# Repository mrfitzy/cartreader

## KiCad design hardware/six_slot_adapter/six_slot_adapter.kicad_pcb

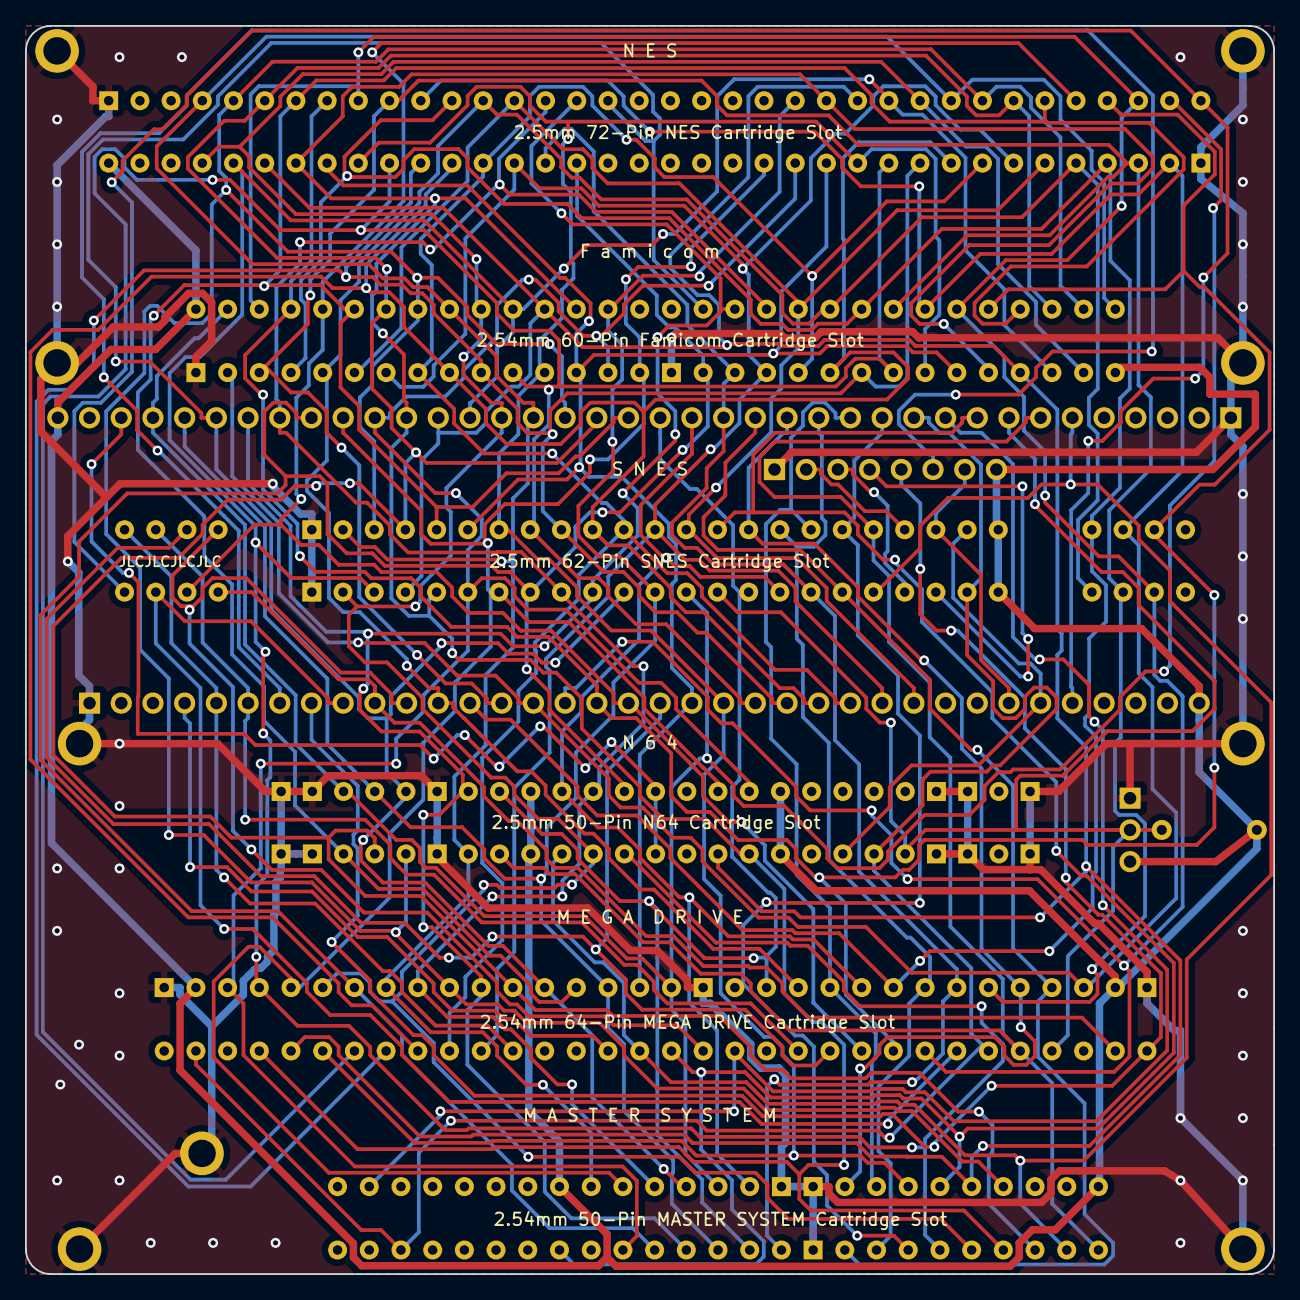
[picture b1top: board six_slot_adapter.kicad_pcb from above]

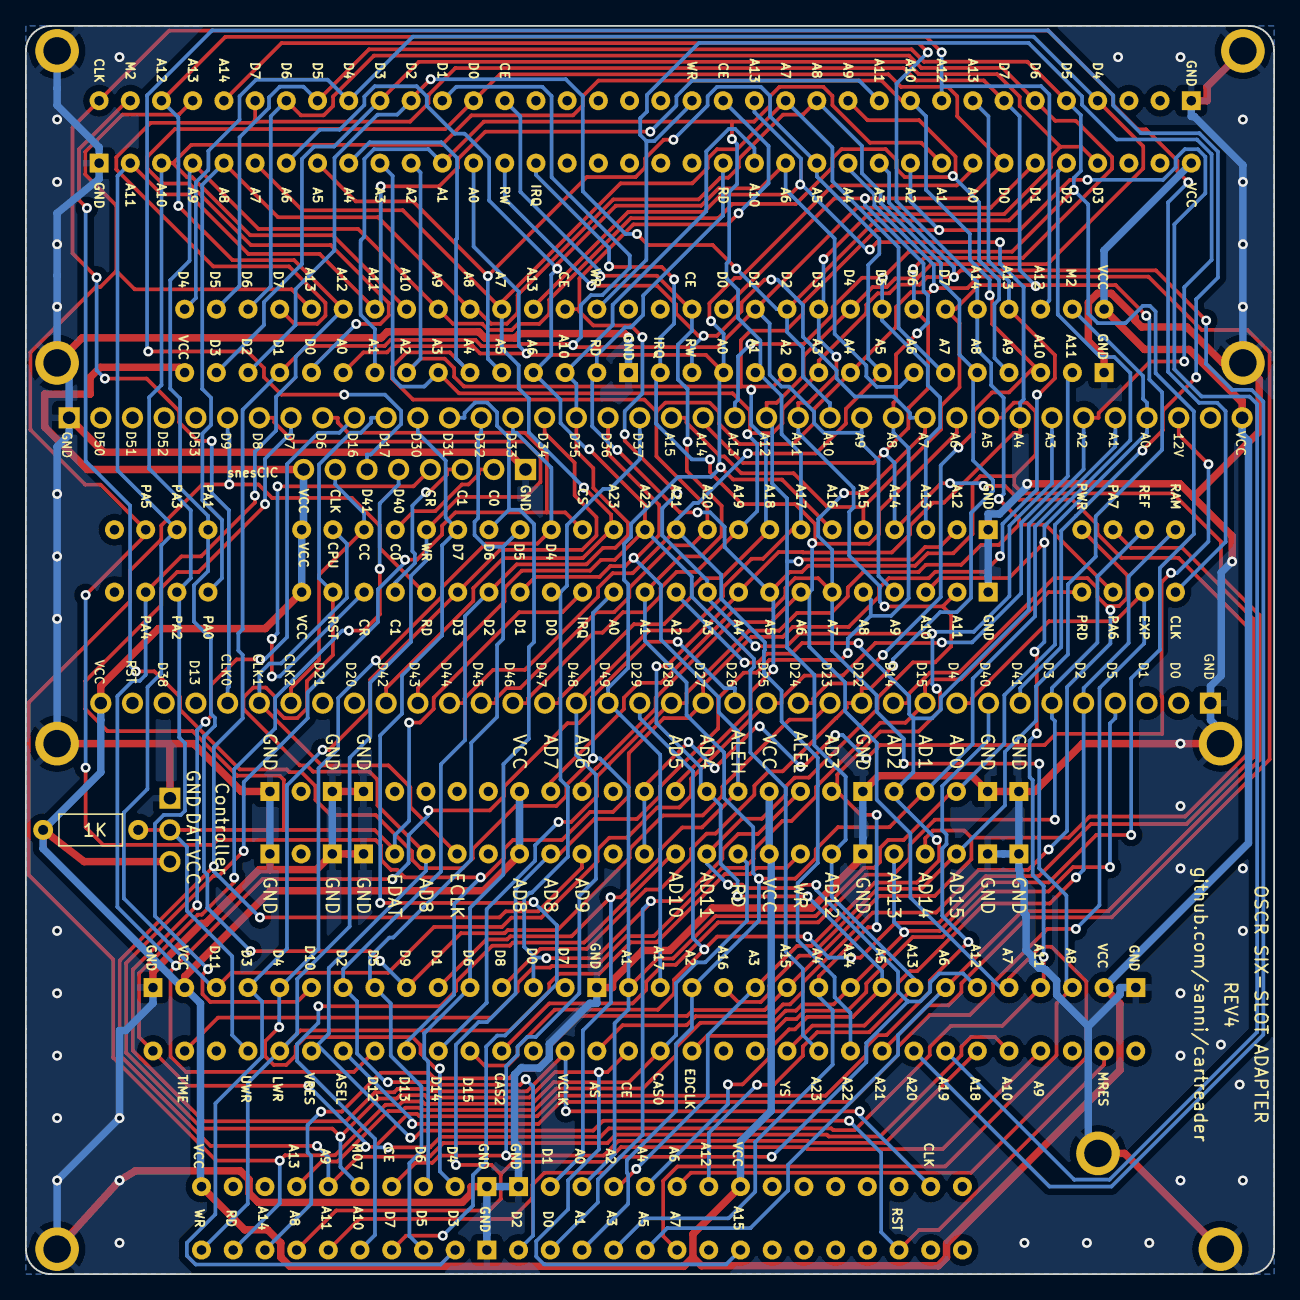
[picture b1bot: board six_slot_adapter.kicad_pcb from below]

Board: 2 copper layers, 100.0 x 100.0 mm, 22 parts (11 on the bottom side), 63 nets.

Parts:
FC1: FC_Slot
J3: CART SLOT TOP ROW; PinSocket_1x38_P2.54mm_Vertical
J4: CART SLOT BOTTOM ROW; PinSocket_1x36_P2.54mm_Vertical
JC1: Controller; PinHeader_1x01_P2.54mm_Vertical
JC2, JC3: Conn_01x01; PinHeader_1x01_P2.54mm_Vertical
JCIC1: Conn_01x08; PinHeader_1x08_P2.54mm_Vertical
M2_1, M2_2, M2_3, M2_4, M2_5, M2_6, M2_7, M2_8, M2_9: Screw_Terminal_01x01; MountingHole_2.2mm_M2_ISO7380_Pad
MD1: MD_Slot
N64: N64_Slot; N64 Slot
NES1: NES_Slot
R1: 1K; R_Axial_DIN0207_L6.3mm_D2.5mm_P10.16mm_Horizontal
SMS1: SMS_Slot
SNES1: SNES_Slot; SNES Slot

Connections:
+12V: J3.3, N64.13 (12V), N64.38 (12V)
A0: FC1.32 (M2), J3.4, MD1.A17 (A1), N64.28 (AD0), NES1.38 (M2), SMS1.25 (A0), SNES1.17 (A0)
A1: FC1.44 (PRG_CE), J3.5, MD1.A15 (A2), N64.29 (AD1), NES1.50 (PRG_CE), SMS1.26 (A1), SNES1.16 (A1)
A2: FC1.47 (CHR_WR), J3.6, MD1.A13 (A3), N64.30 (AD2), NES1.56 (CHR_WR), SMS1.27 (A2), SNES1.15 (A2)
A3: FC1.48 (CIRAM_CE), J3.7, MD1.A11 (A4), N64.32 (AD3), NES1.57 (CIRAM_CE), SMS1.28 (A3), SNES1.14 (A3)
A4: FC1.49 (CHR_/A13), J3.8, MD1.A9 (A5), N64.36 (AD4), NES1.58 (CHR_/A13), SMS1.29 (A4), SNES1.13 (A4)
A5: FC1.17 (CHR_RD), J3.9, MD1.A7 (A6), N64.37 (AD5), NES1.21 (CHR_RD), SMS1.30 (A5), SNES1.12 (A5)
A6: FC1.15 (IRQ), J3.10, MD1.A5 (A7), N64.40 (AD6), NES1.15 (IRQ), SMS1.31 (A6), SNES1.11 (A6)
A7: FC1.14 (PRG_RW), J3.11, MD1.A3 (A8), N64.41 (AD7), NES1.14 (PRG_RW), SMS1.32 (A7), SNES1.10 (A7)
A8: FC1.26 (CHR_D0), FC1.43 (PRG_D0), J3.12, MD1.B4 (A9), N64.16 (AD8), NES1.30 (CHR_D0), NES1.49 (PRG_D0), SMS1.8 (A8), SNES1.9 (A8)
A9: FC1.27 (CHR_D1), FC1.42 (PRG_D1), J3.13, MD1.B5 (A10), N64.15 (AD9), NES1.31 (CHR_D1), NES1.48 (PRG_D1), SMS1.9 (A9), SNES1.8 (A9)
A10: FC1.28 (CHR_D2), FC1.41 (PRG_D2), J3.14, MD1.A4 (A11), N64.12 (AD10), NES1.32 (CHR_D2), NES1.47 (PRG_D2), SMS1.12 (A10), SNES1.7 (A10)
A11: FC1.29 (CHR_D3), FC1.40 (PRG_D3), J3.15, MD1.A6 (A12), N64.11 (AD11), NES1.33 (CHR_D3), NES1.46 (PRG_D3), SMS1.10 (A11), SNES1.6 (A11)
A12: FC1.39 (PRG_D4), FC1.60 (CHR_D4), J3.16, MD1.A8 (A13), N64.7 (AD12), NES1.45 (PRG_D4), NES1.69 (CHR_D4), SMS1.33 (A12), SNES1.37 (A12)
A13: FC1.38 (PRG_D5), FC1.59 (CHR_D5), J3.17, MD1.A10 (A14), N64.5 (AD13), NES1.44 (PRG_D5), NES1.68 (CHR_D5), SMS1.7 (A13), SNES1.38 (A13)
A14: FC1.37 (PRG_D6), FC1.58 (CHR_D6), J3.18, MD1.A12 (A15), N64.4 (AD14), NES1.43 (PRG_D6), NES1.67 (CHR_D6), SMS1.6 (A14), SNES1.39 (A14)
A15: FC1.36 (PRG_D7), FC1.57 (CHR_D7), J3.19, MD1.A14 (A16), N64.3 (AD15), NES1.42 (PRG_D7), NES1.66 (CHR_D7), SNES1.40 (A15)
CIC DATA 0: JCIC1.7, SNES1.55 (CIC_data_out_(p2))
CIC DATA 1: JCIC1.6, SNES1.24 (CIC_out_data_(p1))
CIC RESET: JCIC1.5, SNES1.25 (CIC_in_data_(p7))
CLK0: J4.32, NES1.37 (CLK), SNES1.1 (21.477MHz_Clock)
CLK1: J4.31, N64.19 (EEPROM_CLK), SNES1.57 (CPU_Clock)
CLK2: J4.30, JCIC1.2, SNES1.56 (CIC_clock_in_(p6))
D2: J4.5, MD1.B12 (/YS), SNES1.32 (/WRAM)
D3: J4.6, MD1.B21 (/CAS2), SNES1.33 (Refresh)
D4: J4.9, MD1.B26 (/ASEL), SNES1.2 (Expand)
D5: J4.4, MD1.B15 (EDCLK)
D6: J3.30, MD1.B17 (/CE_0), SMS1.11 (M0-7), SMS1.36 (A15), SNES1.49 (/Cart)
D7: J3.31, JC2.1, MD1.B29 (/UWR), N64.21 (EEPROM_DATA), R1.2, SNES1.18 (/IRQ)
D8: J3.32, MD1.B28 (/LWR), N64.8 (/WRITE), SMS1.2 (WR), SNES1.54 (/WR)
D9: J3.33, MD1.B16 (/CAS0), N64.10 (/READ), SMS1.4 (RD), SNES1.23 (/RD)
D14: J4.11, MD1.B18 (/AS), SNES1.35 (/PAWR)
D15: J4.10, MD1.B31 (/TIME), SNES1.4 (/PARD)
D16: J3.29, MD1.B19 (VCLK), SMS1.47 (Clock)
D17: J3.28, MD1.B2 (/MRES), MD1.B27 (/VRES), N64.20 (RESET), SMS1.46 (Reset), SNES1.26 (/RESET)
D22: FC1.5 (PRG_A8), FC1.51 (CHR_A8), J4.12, MD1.A21 (D8), NES1.5 (PRG_A8), NES1.60 (CHR_A8), SNES1.28 (PA0)
D23: FC1.4 (PRG_A9), FC1.52 (CHR_A9), J4.13, MD1.A24 (D9), NES1.4 (PRG_A9), NES1.61 (CHR_A9), SNES1.59 (PA1)
D24: FC1.3 (PRG_A10), FC1.53 (CHR_A10), J4.14, MD1.A27 (D10), NES1.3 (PRG_A10), NES1.63 (CHR_A10), SNES1.29 (PA2)
D25: FC1.2 (PRG_A11), FC1.54 (CHR_A11), J4.15, MD1.A30 (D11), NES1.2 (PRG_A11), NES1.62 (CHR_A11), SNES1.60 (PA3)
D26: FC1.33 (PRG_A12), FC1.55 (CHR_A12), J4.16, MD1.B25 (D12), NES1.39 (PRG_A12), NES1.64 (CHR_A12), SNES1.30 (PA4)
D27: FC1.34 (PRG_A13), FC1.56 (CHR_A13), J4.17, MD1.B24 (D13), NES1.40 (PRG_A13), NES1.65 (CHR_A13), SNES1.61 (PA5)
D28: FC1.35 (PRG_A14), J4.18, MD1.B23 (D14), NES1.41 (PRG_A14), SNES1.3 (PA6)
D29: J4.19, MD1.B22 (D15), SNES1.34 (PA7)
D30: J3.27, MD1.A19 (D7), SMS1.14 (D7), SNES1.53 (D7)
D31: J3.26, MD1.A22 (D6), SMS1.15 (D6), SNES1.52 (D6)
D32: J3.25, MD1.A25 (D5), SMS1.16 (D5), SNES1.51 (D5)
D33: J3.24, MD1.A28 (D4), SMS1.17 (D4), SNES1.50 (D4)
D34: J3.23, MD1.A29 (D3), SMS1.18 (D3), SNES1.22 (D3)
D35: FC1.18 (CIRAM_A10), J3.22, MD1.A26 (D2), NES1.22 (CIRAM_A10), SMS1.22 (D2), SNES1.21 (D2)
D36: J3.21, MD1.A23 (D1), N64.35 (ALE_H), SMS1.23 (D1), SNES1.20 (D1)
D37: J3.20, MD1.A20 (D0), N64.33 (ALE_L), SMS1.24 (D0), SNES1.19 (D0)
D40: J4.8, JCIC1.4, MD1.B32 (/CART)
D41: J4.7, JCIC1.3
D42: FC1.6 (PRG_A7), FC1.50 (CHR_A7), J4.27, NES1.6 (PRG_A7), NES1.59 (CHR_A7), SNES1.48 (BA7)
D43: FC1.7 (PRG_A6), FC1.19 (CHR_A6), J4.26, MD1.B11 (A23), NES1.7 (PRG_A6), NES1.23 (CHR_A6), SNES1.47 (BA6)
D44: FC1.8 (PRG_A5), FC1.20 (CHR_A5), J4.25, MD1.B10 (A22), NES1.8 (PRG_A5), NES1.24 (CHR_A5), SNES1.46 (BA5)
D45: FC1.9 (PRG_A4), FC1.21 (CHR_A4), J4.24, MD1.B9 (A21), NES1.9 (PRG_A4), NES1.25 (CHR_A4), SNES1.45 (BA4)
D46: FC1.10 (PRG_A3), FC1.22 (CHR_A3), J4.23, MD1.B8 (A20), NES1.10 (PRG_A3), NES1.26 (CHR_A3), SNES1.44 (BA3)
D47: FC1.11 (PRG_A2), FC1.23 (CHR_A2), J4.22, MD1.B7 (A19), NES1.11 (PRG_A2), NES1.27 (CHR_A2), SNES1.43 (BA2)
D48: FC1.12 (PRG_A1), FC1.24 (CHR_A1), J4.21, MD1.B6 (A18), NES1.12 (PRG_A1), NES1.28 (CHR_A1), SMS1.13 (CE), SNES1.42 (BA1)
D49: FC1.13 (PRG_A0), FC1.25 (CHR_A0), J4.20, MD1.A16 (A17), NES1.13 (PRG_A0), NES1.29 (CHR_A0), SNES1.41 (BA0)
GND: FC1.1 (GND), FC1.16 (GND), J3.38, J4.1, JC3.1, JCIC1.8, M2_1.1, M2_2.1, M2_3.1, M2_4.1, M2_5.1, M2_6.1, M2_7.1, M2_8.1, M2_9.1, MD1.A1 (GND), MD1.A18 (GND), MD1.A32 (GND), N64.1 (GND), N64.2 (GND), N64.6 (GND), N64.22 (GND), N64.23 (GND), N64.25 (GND), N64.26 (GND), N64.27 (GND), N64.31 (GND), N64.47 (GND), N64.48 (GND), N64.50 (GND), NES1.1 (GND), NES1.72 (GND), SMS1.19 (GND), SMS1.20 (GND), SMS1.21 (GND), SNES1.5 (GND), SNES1.36 (GND)
VCC: FC1.30 (5V), FC1.31 (VCC), J3.1, J4.36, JC1.1, JCIC1.1, MD1.A2 (VCC), MD1.A31 (VCC), N64.9 (VCC), N64.17 (VCC), N64.34 (VCC), N64.42 (VCC), NES1.36 (VCC), R1.1, SMS1.1 (5V), SMS1.35 (5V), SNES1.27 (VCC), SNES1.58 (VCC)

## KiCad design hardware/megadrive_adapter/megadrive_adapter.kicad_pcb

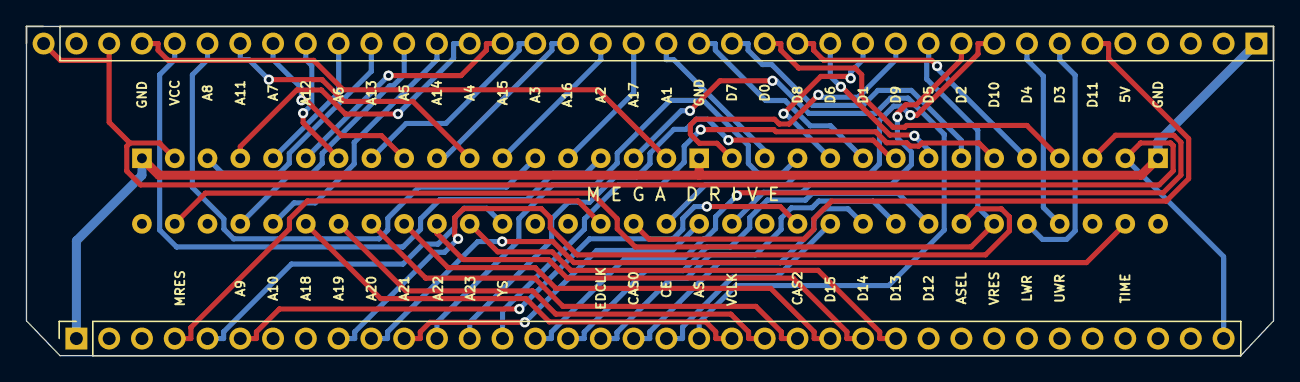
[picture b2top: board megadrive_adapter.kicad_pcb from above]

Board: 2 copper layers, 96.6 x 25.5 mm, 3 parts (0 on the bottom side), 53 nets.

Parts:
J1: CART SLOT TOP ROW; PinSocket_1x38_P2.54mm_Vertical
J2: CART SLOT BOTTOM ROW; PinSocket_1x36_P2.54mm_Vertical
U1: MD_Slot

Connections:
A0: J1.4, U1.A17 (A1)
A1: J1.5, U1.A15 (A2)
A2: J1.6, U1.A13 (A3)
A3: J1.7, U1.A11 (A4)
A4: J1.8, U1.A9 (A5)
A5: J1.9, U1.A7 (A6)
A6: J1.10, U1.A5 (A7)
A7: J1.11, U1.A3 (A8)
A8: J1.12, U1.B4 (A9)
A9: J1.13, U1.B5 (A10)
A10: J1.14, U1.A4 (A11)
A11: J1.15, U1.A6 (A12)
A12: J1.16, U1.A8 (A13)
A13: J1.17, U1.A10 (A14)
A14: J1.18, U1.A12 (A15)
A15: J1.19, U1.A14 (A16)
D2: J2.5, U1.B12 (/YS)
D3: J2.6, U1.B21 (/CAS2)
D4: J2.9, U1.B26 (/ASEL)
D5: J2.4, U1.B15 (EDCLK)
D6: J1.30, U1.B17 (/CE_0)
D7: J1.31, U1.B29 (/UWR)
D8: J1.32, U1.B28 (/LWR)
D9: J1.33, U1.B16 (/CAS0)
D14: J2.11, U1.B18 (/AS)
D15: J2.10, U1.B31 (/TIME)
D16: J1.29, U1.B19 (VCLK)
D17: J1.28, U1.B2 (/MRES), U1.B27 (/VRES)
D22: J2.12, U1.A21 (D8)
D23: J2.13, U1.A24 (D9)
D24: J2.14, U1.A27 (D10)
D25: J2.15, U1.A30 (D11)
D26: J2.16, U1.B25 (D12)
D27: J2.17, U1.B24 (D13)
D28: J2.18, U1.B23 (D14)
D29: J2.19, U1.B22 (D15)
D30: J1.27, U1.A19 (D7)
D31: J1.26, U1.A22 (D6)
D32: J1.25, U1.A25 (D5)
D33: J1.24, U1.A28 (D4)
D34: J1.23, U1.A29 (D3)
D35: J1.22, U1.A26 (D2)
D36: J1.21, U1.A23 (D1)
D37: J1.20, U1.A20 (D0)
D43: J2.26, U1.B11 (A23)
D44: J2.25, U1.B10 (A22)
D45: J2.24, U1.B9 (A21)
D46: J2.23, U1.B8 (A20)
D47: J2.22, U1.B7 (A19)
D48: J2.21, U1.B6 (A18)
D49: J2.20, U1.A16 (A17)
GND: J1.38, J2.1, U1.A1 (GND), U1.A18 (GND), U1.A32 (GND)
VCC: J1.1, J1.3, J2.36, U1.A2 (VCC), U1.A31 (VCC)

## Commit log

2024-01-24 config: set v5, GBx only, no vselect, no clockgen
2024-01-24 gb: experiment with SST 39SF010A cart
2024-01-24 gb 39SF010A: successful write experimenet
2024-01-24 gb 39SF010A: add flash support
2024-02-09 fw: enable vselect, megadrive
2024-02-09 megadrive adapter: update main label; -> kicad v7
2024-02-09 six-slot adapter: update labels; -> kicad v7
2024-08-18 (wip) GB: 39SF040 flash support
2024-08-18 fw: enable rtc, clockgen
2024-08-18 fw: post-merge fixes (ENABLE_FLASH)
2026-01-23 config: enable rtc, flash, n64, nes, sms
2026-01-23 main menu: add SD card browser
